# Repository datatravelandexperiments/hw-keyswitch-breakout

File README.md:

Keyswitch Breakout Boards
=========================

**This is a work in progress, and the hardware/software described here has not been shown to work correctly.**

These small boards are designed to adapt [Cherry MX](http://www.cherrycorp.com/english/switches/key/mx.htm) and ALPS SKC keyswitches to standard 0.1″ breadboards.

The center of the keyswitch is offset by 0.025″ on each axis from the 0.1″ breadboard grid. This allows for adjacent keys at 0.75″ spacing to be mounted on a 0.1″ breadboard by rotating successive units 90°.

For the Cherry MX, a matrix diode can be installed either in the switch (through hole) or on the breakout board (surface mount); the ALPS board only has room for an SMD matrix diode. Both allow mounting an LED of the appropriate type — 3mm round for Cherry MX, 2mm × 5mm rectangle for APLS. (APLS variants with click plates have no room for an LED.)

The boards also have pins that bypass any installed matrix diode.

Except for the LED, all connections are duplicated at two or three points to simplify building a matrix.

Schematics and boards are in [Eagle CAD](http://www.cadsoftusa.com/download-eagle/) format.

<!-- vim:set et sts=4 sw=4 linebreak ft=ghmarkdown: -->

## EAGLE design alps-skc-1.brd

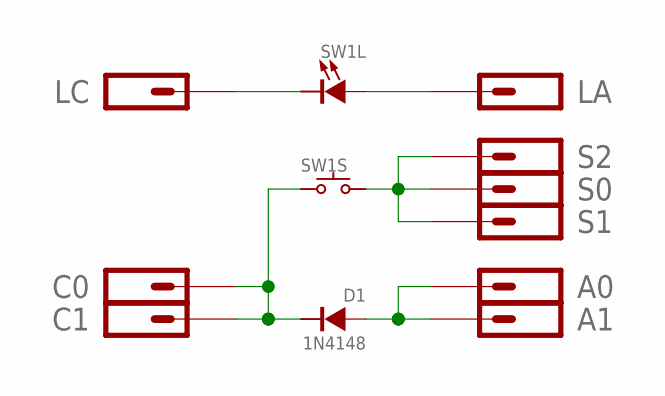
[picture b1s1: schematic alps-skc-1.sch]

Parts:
A0: J-1-SQUARE-70
A1: J-1-SQUARE-74
C0: J-1-SQUARE-70
C1: J-1-SQUARE-74
D1: 1N4148; SMA+SOD323-P-NOSS
LA: J-1-OCTAGON-70
LC: J-1-OCTAGON-70
S0: J-1-ROUND-70
S1, S2: J-1-ROUND-74
SW1: SW-ALPS-SKC-LED

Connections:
A: A0.1, A1.1, D1.A
C: C0.1, C1.1, D1.C, SW1.S1 (1)
LA: LA.1, SW1.LA (A)
LC: LC.1, SW1.LC (C)
S: S0.1, S1.1, S2.1, SW1.S2 (2)

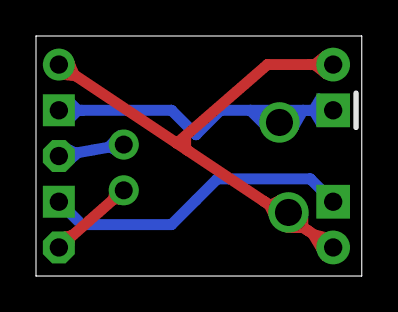
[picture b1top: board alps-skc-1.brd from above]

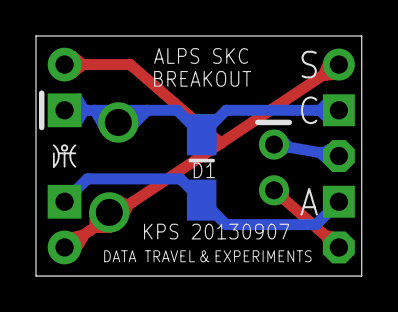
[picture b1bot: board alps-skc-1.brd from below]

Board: 2 copper layers, 18.1 x 13.3 mm, 12 parts (2 on the bottom side), 5 nets.

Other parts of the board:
U$1: GLYPH-DT&E-50

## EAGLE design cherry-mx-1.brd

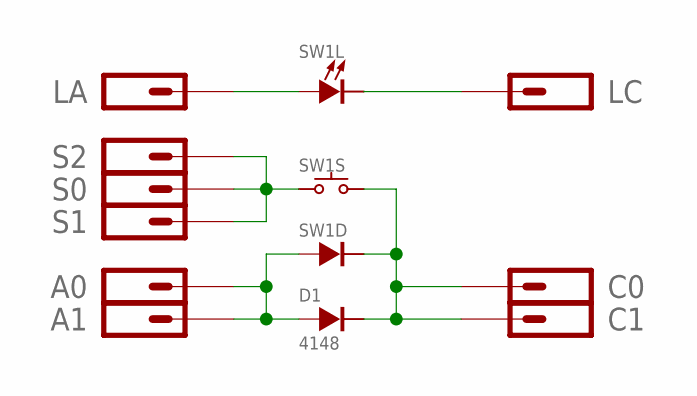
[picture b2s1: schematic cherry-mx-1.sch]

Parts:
A0: J-1-SQUARE-70
A1: J-1-SQUARE-74
C0: J-1-SQUARE-70
C1: J-1-SQUARE-74
D1: 4148; SMA+SOD323-P-NOSS
LA: J-1-OCTAGON-70
LC: J-1-OCTAGON-70
S0: J-1-ROUND-70
S1, S2: J-1-ROUND-74
SW1: SW-CHERRY-MX-BOTH

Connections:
A: A0.1, A1.1, D1.A, SW1.A
C: C0.1, C1.1, D1.C, SW1.C, SW1.S2 (2)
LA: LA.1, SW1.LA (A)
LC: LC.1, SW1.LC (C)
S: S0.1, S1.1, S2.1, SW1.S1 (1)

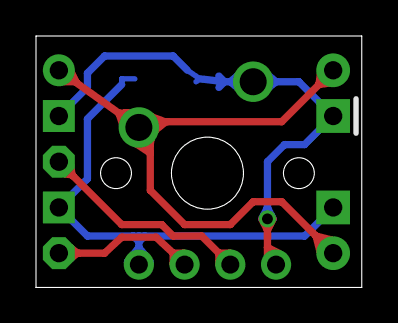
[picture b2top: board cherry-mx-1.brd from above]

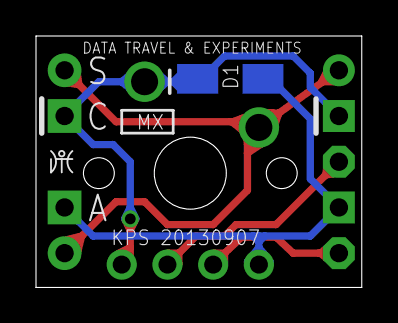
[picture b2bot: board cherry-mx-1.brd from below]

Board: 2 copper layers, 18.1 x 14.0 mm, 12 parts (2 on the bottom side), 5 nets.

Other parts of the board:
U$1: GLYPH-DT&E-50

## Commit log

2013-09-10 This is a commit message. There are many like it, but this one is mine.
